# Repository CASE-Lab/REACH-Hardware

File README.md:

# REACH-Hardware
REACH - Rugged Extensible Autonomous Control Hardware

## The REACH Unit
Is a fairly compact linux computer built upon the Nvidia Xavier NX developer kit. The main idea is to make the developer kit rugged and modular/extensible. 

### Fields of Interest
The unit is supposed to be used in the fields of robotics and automation if more robust and/or modular solution is needed. 

Example: A REACH unit is used in a research project with an autonomous jet ski. The rugged enclosure makes it ideal for the harsh environment. Because of it's modularity it also allows for future extensions to meet new needs that can arise. This version of the unit features two camera inputs and telemetry support.

Example: A REACH unit is used for controlling a Husqvarna Research Platform (HRP) (a modified robotic lawn mower for research purposes). It allows for enough computational power to easily run ROS2, while also allowing for a camera and USB devices to be connected in the future. This version of the unit is the standard version with one camera input and GPIO ports.

### Features
* Built upon an Nvidia NX developer kit
* Passively cooled
* Should attain an IP65 rating (untested)
* Allows for use of up to two Raspberry PI cameras over a distance of up to 10m using the HDMI to CSI adapter (adapter found in REACH-Extensions). (Number of supported cameras varies depending on the configuration)
* All standard connectors from the dev kit have been routed to the outside of the enclosure (1x Ethernet port, Wifi, 2-3x USB ports)
* Features up to 4 expansion cards which can add function such as CAN and RS232 support. Each card can be conencted to a standard M12 industrial connector located on the front panel.
* Depending on the configuration the unit features either 2 analogue and 5 digital GPIO pins or telemetry support.

[TOC]

## Getting Started

### Flashing with Nvidia SDK

* Currently requires Ubuntu 18.04 for Nvidia SDK Manager
* Can also be used on newer Ubuntu versions via Docker. [Instructions](https://docs.nvidia.com/sdk-manager/docker-containers/index.html)

### Booting from NVME SSD

* [Jetsonhacks Guide](https://www.jetsonhacks.com/2020/05/29/jetson-xavier-nx-run-from-ssd/)

### Stress testing

* Monitoring using jtop (requires pip for installation)

  ```sh
  # install
  sudo -H pip install -U jetson-stats
  # run
  sudo jtop
  ```

* Stress test GPU (and also CPU indirectly by running multiple instances of glmark2)

  ```sh
  # install
  sudo apt-get install -y glmark2
  # run
  glmark2
  ```

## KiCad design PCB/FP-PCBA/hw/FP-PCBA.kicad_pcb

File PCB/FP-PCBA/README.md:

# FP-PCBA

Front Panel PCB Assembly

* Breaks out USB 3.0 from Jetson development board to front panel
* Holds 4 modular expansion headers

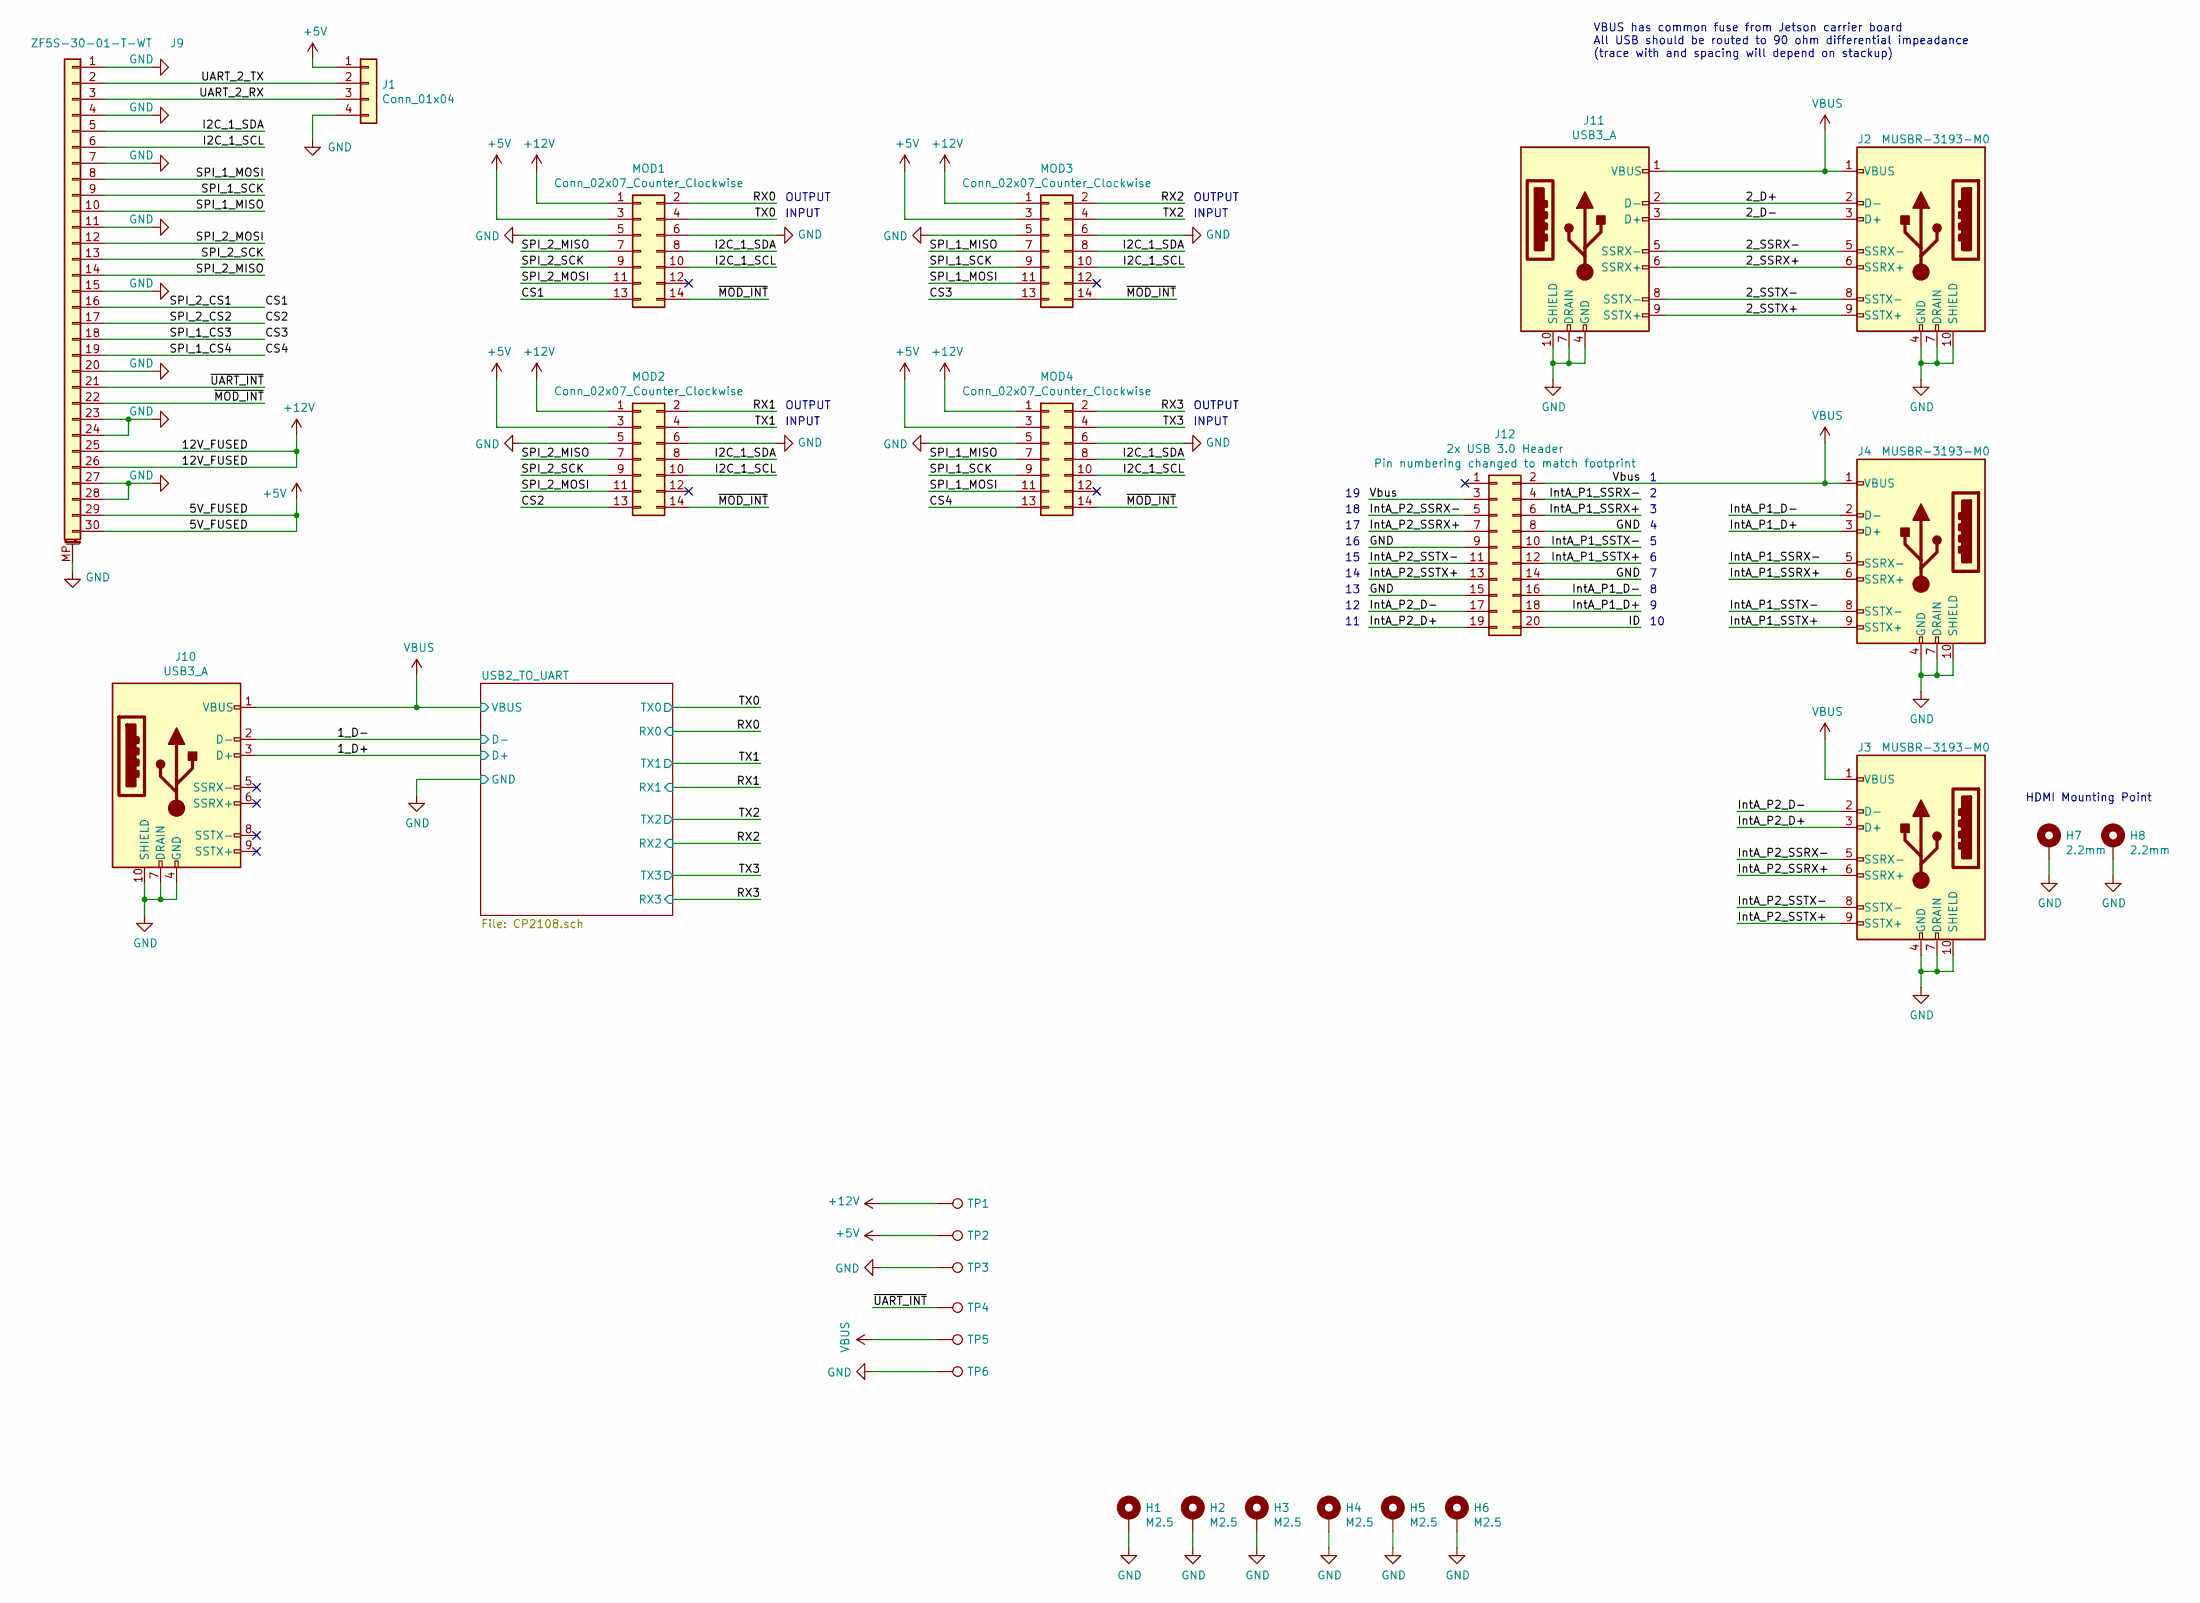
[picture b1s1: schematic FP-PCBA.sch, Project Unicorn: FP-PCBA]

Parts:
H1, H2, H3, H4: M2.5; MountingHole_2.7mm_M2.5_Pad_Via
H5, H6: M2.5; Slotted_2mm_M2.5_Vias
H7, H8: 2.2mm; MountingHole_2.2mm_M2_Pad
J1: Conn_01x04; Molex_Micro_Lock_1x4_Vertical_5055680471; MPN 505568-0471
J2, J3, J4: MUSBR-3193-M0; MUSBR3193M0; MPN MUSBR-3193-M0
J9: ZF5S-30-01-T-WT; ZF5S-30-03-T-WT; MPN ZF5S-30-03-T-WT
J10, J11: USB3_A; USB3_A_Plug_AMPHENOL_GSB316441CEU; MPN GSB316441CEU
J12: 2x USB 3.0 Header; PinHeader_2x10_P2.00mm_Vertical; MPN TW-10-11-T-D-250-080
MOD1, MOD2, MOD3, MOD4: Conn_02x07_Counter_Clockwise; Samtec_HLE-107-02-xxx-DV-BE-A_2x07_P2.54mm_Horizontal; MPN HLE-107-02-F-DV-BE-A-K-TR
TP1, TP2, TP3, TP4, TP5, TP6: TestPoint; TestPoint_THTPad_D1.0mm_Drill0.5mm

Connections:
+5V: J1.1, J9.29, J9.30, MOD1.3, MOD2.3, MOD3.3, MOD4.3, TP2.1
+12V: J9.25, J9.26, MOD1.1, MOD2.1, MOD3.1, MOD4.1, TP1.1
/1_D+: J10.3 (D+); also elsewhere on the board
/1_D-: J10.2 (D-); also elsewhere on the board
/2_D+: J2.2 (D-), J11.2 (D-)
/2_D-: J2.3 (D+), J11.3 (D+)
/2_SSRX+: J2.6 (SSRX+), J11.6 (SSRX+)
/2_SSRX-: J2.5 (SSRX-), J11.5 (SSRX-)
/2_SSTX+: J2.9 (SSTX+), J11.9 (SSTX+)
/2_SSTX-: J2.8 (SSTX-), J11.8 (SSTX-)
/CS1: J9.16, MOD1.13
/CS2: J9.17, MOD2.13
/CS3: J9.18, MOD3.13
/CS4: J9.19, MOD4.13
/I2C_1_SCL: J9.6, MOD1.10, MOD2.10, MOD3.10, MOD4.10
/I2C_1_SDA: J9.5, MOD1.8, MOD2.8, MOD3.8, MOD4.8
/ID: J12.20
/IntA_P1_D+: J4.3 (D+), J12.18
/IntA_P1_D-: J4.2 (D-), J12.16
/IntA_P1_SSRX+: J4.6 (SSRX+), J12.6
/IntA_P1_SSRX-: J4.5 (SSRX-), J12.4
/IntA_P1_SSTX+: J4.9 (SSTX+), J12.12
/IntA_P1_SSTX-: J4.8 (SSTX-), J12.10
/IntA_P2_D+: J3.3 (D+), J12.19
/IntA_P2_D-: J3.2 (D-), J12.17
/IntA_P2_SSRX+: J3.6 (SSRX+), J12.7
/IntA_P2_SSRX-: J3.5 (SSRX-), J12.5
/IntA_P2_SSTX+: J3.9 (SSTX+), J12.13
/IntA_P2_SSTX-: J3.8 (SSTX-), J12.11
/RX0: MOD1.2; also elsewhere on the board
/RX1: MOD2.2; also elsewhere on the board
/RX2: MOD3.2; also elsewhere on the board
/RX3: MOD4.2; also elsewhere on the board
/SPI_1_MISO: J9.10, MOD3.7, MOD4.7
/SPI_1_MOSI: J9.8, MOD3.11, MOD4.11
/SPI_1_SCK: J9.9, MOD3.9, MOD4.9
/SPI_2_MISO: J9.14, MOD1.7, MOD2.7
/SPI_2_MOSI: J9.12, MOD1.11, MOD2.11
/SPI_2_SCK: J9.13, MOD1.9, MOD2.9
/TX0: MOD1.4; also elsewhere on the board
/TX1: MOD2.4; also elsewhere on the board
/TX2: MOD3.4; also elsewhere on the board
/TX3: MOD4.4; also elsewhere on the board
/UART_2_RX: J1.3, J9.3
/UART_2_TX: J1.2, J9.2
/~MOD_INT: J9.22, MOD1.14, MOD2.14, MOD3.14, MOD4.14
/~UART_INT: J9.21, TP4.1
GND: H1.1, H2.1, H3.1, H4.1, H5.1, H6.1, H7.1, H8.1, J1.4, J2.4 (GND), J2.7 (DRAIN), J2.10 (SHIELD), J3.4 (GND), J3.7 (DRAIN), J3.10 (SHIELD), J4.4 (GND), J4.7 (DRAIN), J4.10 (SHIELD), J9.1, J9.4, J9.7, J9.11, J9.15, J9.20, J9.23, J9.24, J9.27, J9.28, J9.MP (MountPin), J10.4 (GND), J10.7 (DRAIN), J10.10 (SHIELD), J11.4 (GND), J11.7 (DRAIN), J11.10 (SHIELD), J12.8, J12.9, J12.14, J12.15, MOD1.5, MOD1.6, MOD2.5, MOD2.6, MOD3.5, MOD3.6, MOD4.5, MOD4.6, TP3.1, TP6.1; also elsewhere on the board
VBUS: J2.1 (VBUS), J3.1 (VBUS), J4.1 (VBUS), J10.1 (VBUS), J11.1 (VBUS), J12.2, J12.3, TP5.1; also elsewhere on the board

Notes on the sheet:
VBUS has common fuse from Jetson carrier board All USB should be routed to 90 ohm differential impeadance (trace with and spacing will depend on stackup)
HDMI Mounting Point
OUTPUT
INPUT

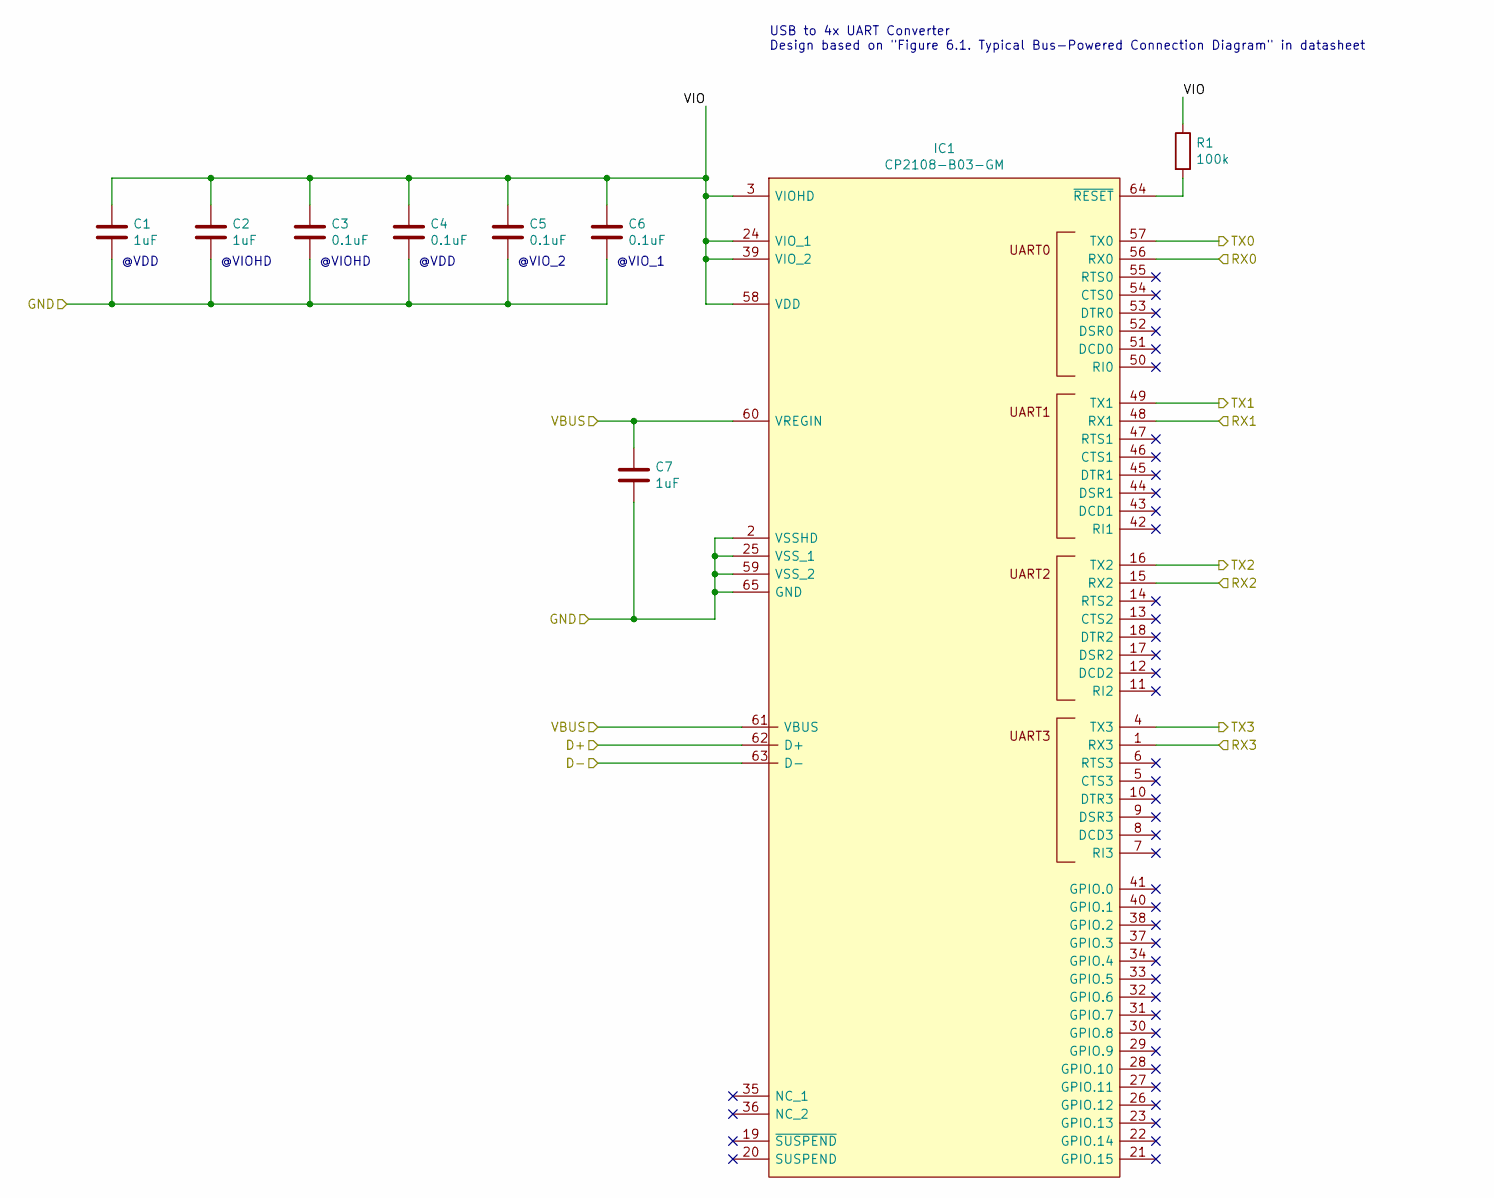
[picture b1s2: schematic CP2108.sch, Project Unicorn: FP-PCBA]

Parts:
C1, C2, C7: 1uF; C_0603_1608Metric; MPN C0603C105K4RAC7411
C3, C4, C5, C6: 0.1uF; C_0603_1608Metric; MPN 06033C104KAT4A
IC1: CP2108-B03-GM; MPN CP2108-B02-GMR
R1: 100k; R_0603_1608Metric

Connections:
/1_D+: IC1.62 (D+); also elsewhere on the board
/1_D-: IC1.63 (D-); also elsewhere on the board
/RX0: IC1.56 (RX0); also elsewhere on the board
/RX1: IC1.48 (RX1); also elsewhere on the board
/RX2: IC1.15 (RX2); also elsewhere on the board
/RX3: IC1.1 (RX3); also elsewhere on the board
/TX0: IC1.57 (TX0); also elsewhere on the board
/TX1: IC1.49 (TX1); also elsewhere on the board
/TX2: IC1.16 (TX2); also elsewhere on the board
/TX3: IC1.4 (TX3); also elsewhere on the board
/USB2_TO_UART/VIO: C1.1, C2.1, C3.1, C4.1, C5.1, C6.1, IC1.3 (VIOHD), IC1.24 (VIO_1), IC1.39 (VIO_2), IC1.58 (VDD), R1.1
GND: C1.2, C2.2, C3.2, C4.2, C5.2, C6.2, C7.2, IC1.2 (VSSHD), IC1.25 (VSS_1), IC1.59 (VSS_2), IC1.65 (GND); also elsewhere on the board
unnamed: IC1.64 (~RESET), R1.2
VBUS: C7.1, IC1.60 (VREGIN), IC1.61 (VBUS); also elsewhere on the board

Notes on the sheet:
@VIO_1
@VIO_2
@VDD
@VIOHD
USB to 4x UART Converter Design based on "Figure 6.1. Typical Bus-Powered Connection Diagram" in datasheet

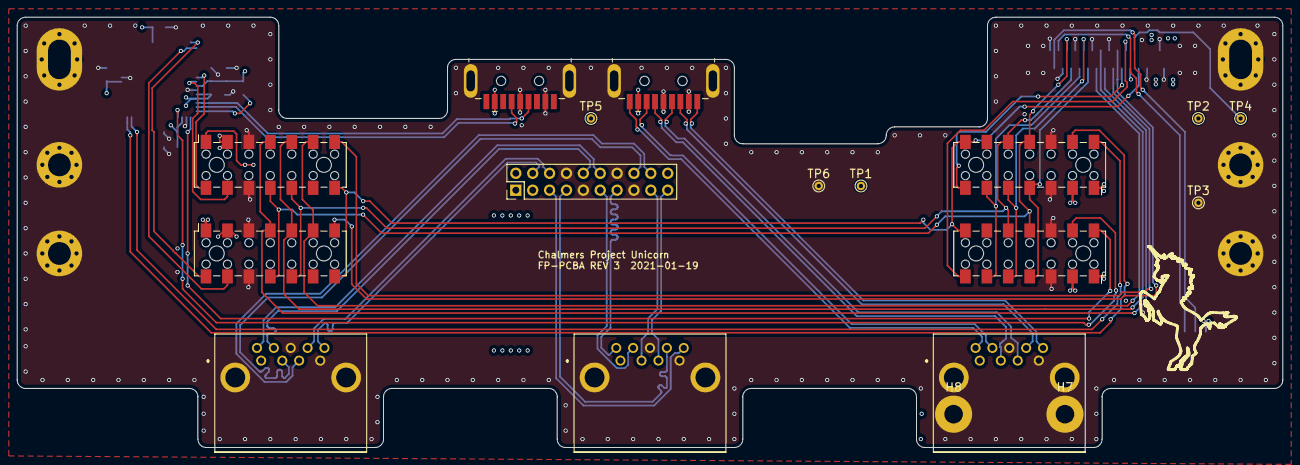
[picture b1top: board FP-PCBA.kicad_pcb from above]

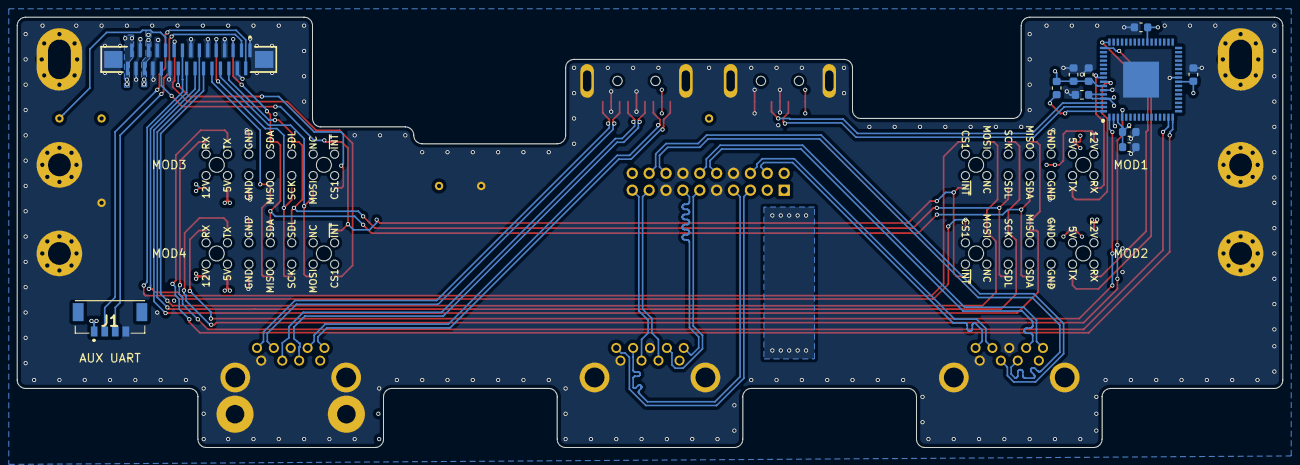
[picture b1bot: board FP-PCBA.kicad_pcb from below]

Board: 4 copper layers, 150.0 x 51.0 mm, 35 parts (11 on the bottom side), 50 nets.

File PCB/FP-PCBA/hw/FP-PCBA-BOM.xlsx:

Project Unicorn: FP-PCBA BOM |  | Chalmers University of Technology
REV: 2 |  | REV Date: 2020-11-12
Reference | Qty | Value | Distributor | Distributor PN | MPN | Manufacturer | DNP | Comments
Non PCB Items
Kicad CSV Imported Items
C4 C5 C6 C3 | 4 | 0.1uF | Mouser | 581-06033C104KAT4A | 06033C104KAT4A | AVX
C7 C2 C1 | 3 | 1uF | Mouser | 80-C0603C105K4RLR | C0603C105K4RAC7411 | KEMET
H1 H2 H3 H4 | 4 | M2.5 |  |  |  |  | DNP
H5 H6 | 2 | M2.5 |  |  |  |  | DNP
H7 H8 | 2 | 2.2mm |  |  |  |  | DNP
IC1 | 1 | CP2108-B03-GM | Mouser | 634-CP2108-B02-GMR | CP2108-B02-GMR | Silicon Labs |  | Change to B03 variant (currently not in stock)
J1 | 1 | Conn_01x04 | Mouser | 538-505568-0471 | 505568-0471 | Molex | DNP | Only populate if used
J10 J11 | 2 | USB3_A | Mouser | 523-GSB316441CEU | GSB316441CEU | Amphenol
J12 | 1 | 2x USB 3.0 Header | Mouser | 200-TW1011TD250080 | TW-10-11-T-D-250-080 | Samtec |  | Pin numbering changed to match footprint
J4 J3 J2 | 3 | MUSBR-3193-M0 | Mouser | 523-MUSBR-3193-M0 | MUSBR-3193-M0 | Amphenol
J9 | 1 | ZF5S-30-01-T-WT | Mouser | 200-ZF5S3003TWTTR | ZF5S-30-03-T-WT | Samtec |  | To FP-PCBA
MOD4 MOD3 MOD2 MOD1 | 4 | Conn_02x07_Counter_Clockwise | Mouser | 200-HLE1072FDVBEAKTR | HLE-107-02-F-DV-BE-A-K-TR | Samtec |  | Check datasheet for compatible variants
R1 | 1 | 100k | CASE
TP3 TP2 TP1 TP5 TP4 TP6 | 6 | TestPoint |  |  |  |  | DNP
0 | 0 | 0 | 0 | 0 | 0 | 0 | 0 | 0
0 | 0 | 0 | 0 | 0 | 0 | 0 | 0 | 0
0 | 0 | 0 | 0 | 0 | 0 | 0 | 0 | 0
0 | 0 | 0 | 0 | 0 | 0 | 0 | 0 | 0
0 | 0 | 0 | 0 | 0 | 0 | 0 | 0 | 0
0 | 0 | 0 | 0 | 0 | 0 | 0 | 0 | 0
0 | 0 | 0 | 0 | 0 | 0 | 0 | 0 | 0
0 | 0 | 0 | 0 | 0 | 0 | 0 | 0 | 0
0 | 0 | 0 | 0 | 0 | 0 | 0 | 0 | 0
0 | 0 | 0 | 0 | 0 | 0 | 0 | 0 | 0
0 | 0 | 0 | 0 | 0 | 0 | 0 | 0 | 0
0 | 0 | 0 | 0 | 0 | 0 | 0 | 0 | 0
0 | 0 | 0 | 0 | 0 | 0 | 0 | 0 | 0
0 | 0 | 0 | 0 | 0 | 0 | 0 | 0 | 0
0 | 0 | 0 | 0 | 0 | 0 | 0 | 0 | 0
0 | 0 | 0 | 0 | 0 | 0 | 0 | 0 | 0
0 | 0 | 0 | 0 | 0 | 0 | 0 | 0 | 0
0 | 0 | 0 | 0 | 0 | 0 | 0 | 0 | 0
0 | 0 | 0 | 0 | 0 | 0 | 0 | 0 | 0
0 | 0 | 0 | 0 | 0 | 0 | 0 | 0 | 0
0 | 0 | 0 | 0 | 0 | 0 | 0 | 0 | 0
0 | 0 | 0 | 0 | 0 | 0 | 0 | 0 | 0
0 | 0 | 0 | 0 | 0 | 0 | 0 | 0 | 0
0 | 0 | 0 | 0 | 0 | 0 | 0 | 0 | 0
0 | 0 | 0 | 0 | 0 | 0 | 0 | 0 | 0
0 | 0 | 0 | 0 | 0 | 0 | 0 | 0 | 0
0 | 0 | 0 | 0 | 0 | 0 | 0 | 0 | 0
0 | 0 | 0 | 0 | 0 | 0 | 0 | 0 | 0
0 | 0 | 0 | 0 | 0 | 0 | 0 | 0 | 0
0 | 0 | 0 | 0 | 0 | 0 | 0 | 0 | 0
0 | 0 | 0 | 0 | 0 | 0 | 0 | 0 | 0
0 | 0 | 0 | 0 | 0 | 0 | 0 | 0 | 0
0 | 0 | 0 | 0 | 0 | 0 | 0 | 0 | 0
0 | 0 | 0 | 0 | 0 | 0 | 0 | 0 | 0
0 | 0 | 0 | 0 | 0 | 0 | 0 | 0 | 0
0 | 0 | 0 | 0 | 0 | 0 | 0 | 0 | 0
0 | 0 | 0 | 0 | 0 | 0 | 0 | 0 | 0
0 | 0 | 0 | 0 | 0 | 0 | 0 | 0 | 0
0 | 0 | 0 | 0 | 0 | 0 | 0 | 0 | 0
0 | 0 | 0 | 0 | 0 | 0 | 0 | 0 | 0
0 | 0 | 0 | 0 | 0 | 0 | 0 | 0 | 0
0 | 0 | 0 | 0 | 0 | 0 | 0 | 0 | 0
0 | 0 | 0 | 0 | 0 | 0 | 0 | 0 | 0
0 | 0 | 0 | 0 | 0 | 0 | 0 | 0 | 0
0 | 0 | 0 | 0 | 0 | 0 | 0 | 0 | 0
0 | 0 | 0 | 0 | 0 | 0 | 0 | 0 | 0
0 | 0 | 0 | 0 | 0 | 0 | 0 | 0 | 0
0 | 0 | 0 | 0 | 0 | 0 | 0 | 0 | 0
0 | 0 | 0 | 0 | 0 | 0 | 0 | 0 | 0
0 | 0 | 0 | 0 | 0 | 0 | 0 | 0 | 0
0 | 0 | 0 | 0 | 0 | 0 | 0 | 0 | 0
0 | 0 | 0 | 0 | 0 | 0 | 0 | 0 | 0
0 | 0 | 0 | 0 | 0 | 0 | 0 | 0 | 0
0 | 0 | 0 | 0 | 0 | 0 | 0 | 0 | 0
0 | 0 | 0 | 0 | 0 | 0 | 0 | 0 | 0
0 | 0 | 0 | 0 | 0 | 0 | 0 | 0 | 0
0 | 0 | 0 | 0 | 0 | 0 | 0 | 0 | 0
0 | 0 | 0 | 0 | 0 | 0 | 0 | 0 | 0
0 | 0 | 0 | 0 | 0 | 0 | 0 | 0 | 0
0 | 0 | 0 | 0 | 0 | 0 | 0 | 0 | 0
0 | 0 | 0 | 0 | 0 | 0 | 0 | 0 | 0
0 | 0 | 0 | 0 | 0 | 0 | 0 | 0 | 0
0 | 0 | 0 | 0 | 0 | 0 | 0 | 0 | 0
0 | 0 | 0 | 0 | 0 | 0 | 0 | 0 | 0
0 | 0 | 0 | 0 | 0 | 0 | 0 | 0 | 0
0 | 0 | 0 | 0 | 0 | 0 | 0 | 0 | 0
0 | 0 | 0 | 0 | 0 | 0 | 0 | 0 | 0
0 | 0 | 0 | 0 | 0 | 0 | 0 | 0 | 0
0 | 0 | 0 | 0 | 0 | 0 | 0 | 0 | 0
0 | 0 | 0 | 0 | 0 | 0 | 0 | 0 | 0
0 | 0 | 0 | 0 | 0 | 0 | 0 | 0 | 0
0 | 0 | 0 | 0 | 0 | 0 | 0 | 0 | 0
0 | 0 | 0 | 0 | 0 | 0 | 0 | 0 | 0
0 | 0 | 0 | 0 | 0 | 0 | 0 | 0 | 0
0 | 0 | 0 | 0 | 0 | 0 | 0 | 0 | 0
0 | 0 | 0 | 0 | 0 | 0 | 0 | 0 | 0
0 | 0 | 0 | 0 | 0 | 0 | 0 | 0 | 0
0 | 0 | 0 | 0 | 0 | 0 | 0 | 0 | 0
0 | 0 | 0 | 0 | 0 | 0 | 0 | 0 | 0
0 | 0 | 0 | 0 | 0 | 0 | 0 | 0 | 0
0 | 0 | 0 | 0 | 0 | 0 | 0 | 0 | 0
0 | 0 | 0 | 0 | 0 | 0 | 0 | 0 | 0
0 | 0 | 0 | 0 | 0 | 0 | 0 | 0 | 0
0 | 0 | 0 | 0 | 0 | 0 | 0 | 0 | 0
0 | 0 | 0 | 0 | 0 | 0 | 0 | 0 | 0
0 | 0 | 0 | 0 | 0 | 0 | 0 | 0 | 0
0 | 0 | 0 | 0 | 0 | 0 | 0 | 0 | 0
0 | 0 | 0 | 0 | 0 | 0 | 0 | 0 | 0
0 | 0 | 0 | 0 | 0 | 0 | 0 | 0 | 0
0 | 0 | 0 | 0 | 0 | 0 | 0 | 0 | 0
0 | 0 | 0 | 0 | 0 | 0 | 0 | 0 | 0
0 | 0 | 0 | 0 | 0 | 0 | 0 | 0 | 0
0 | 0 | 0 | 0 | 0 | 0 | 0 | 0 | 0
0 | 0 | 0 | 0 | 0 | 0 | 0 | 0 | 0
0 | 0 | 0 | 0 | 0 | 0 | 0 | 0 | 0
0 | 0 | 0 | 0 | 0 | 0 | 0 | 0 | 0
0 | 0 | 0 | 0 | 0 | 0 | 0 | 0 | 0
0 | 0 | 0 | 0 | 0 | 0 | 0 | 0 | 0
0 | 0 | 0 | 0 | 0 | 0 | 0 | 0 | 0
0 | 0 | 0 | 0 | 0 | 0 | 0 | 0 | 0
0 | 0 | 0 | 0 | 0 | 0 | 0 | 0 | 0
0 | 0 | 0 | 0 | 0 | 0 | 0 | 0 | 0
0 | 0 | 0 | 0 | 0 | 0 | 0 | 0 | 0
0 | 0 | 0 | 0 | 0 | 0 | 0 | 0 | 0
0 | 0 | 0 | 0 | 0 | 0 | 0 | 0 | 0
0 | 0 | 0 | 0 | 0 | 0 | 0 | 0 | 0
0 | 0 | 0 | 0 | 0 | 0 | 0 | 0 | 0
0 | 0 | 0 | 0 | 0 | 0 | 0 | 0 | 0
0 | 0 | 0 | 0 | 0 | 0 | 0 | 0 | 0
0 | 0 | 0 | 0 | 0 | 0 | 0 | 0 | 0
0 | 0 | 0 | 0 | 0 | 0 | 0 | 0 | 0
0 | 0 | 0 | 0 | 0 | 0 | 0 | 0 | 0
0 | 0 | 0 | 0 | 0 | 0 | 0 | 0 | 0
0 | 0 | 0 | 0 | 0 | 0 | 0 | 0 | 0
0 | 0 | 0 | 0 | 0 | 0 | 0 | 0 | 0
0 | 0 | 0 | 0 | 0 | 0 | 0 | 0 | 0
0 | 0 | 0 | 0 | 0 | 0 | 0 | 0 | 0
0 | 0 | 0 | 0 | 0 | 0 | 0 | 0 | 0
0 | 0 | 0 | 0 | 0 | 0 | 0 | 0 | 0
0 | 0 | 0 | 0 | 0 | 0 | 0 | 0 | 0
0 | 0 | 0 | 0 | 0 | 0 | 0 | 0 | 0
0 | 0 | 0 | 0 | 0 | 0 | 0 | 0 | 0
0 | 0 | 0 | 0 | 0 | 0 | 0 | 0 | 0
0 | 0 | 0 | 0 | 0 | 0 | 0 | 0 | 0
0 | 0 | 0 | 0 | 0 | 0 | 0 | 0 | 0
0 | 0 | 0 | 0 | 0 | 0 | 0 | 0 | 0
0 | 0 | 0 | 0 | 0 | 0 | 0 | 0 | 0
0 | 0 | 0 | 0 | 0 | 0 | 0 | 0 | 0
0 | 0 | 0 | 0 | 0 | 0 | 0 | 0 | 0
0 | 0 | 0 | 0 | 0 | 0 | 0 | 0 | 0
0 | 0 | 0 | 0 | 0 | 0 | 0 | 0 | 0
0 | 0 | 0 | 0 | 0 | 0 | 0 | 0 | 0
0 | 0 | 0 | 0 | 0 | 0 | 0 | 0 | 0
0 | 0 | 0 | 0 | 0 | 0 | 0 | 0 | 0
0 | 0 | 0 | 0 | 0 | 0 | 0 | 0 | 0
0 | 0 | 0 | 0 | 0 | 0 | 0 | 0 | 0
0 | 0 | 0 | 0 | 0 | 0 | 0 | 0 | 0
0 | 0 | 0 | 0 | 0 | 0 | 0 | 0 | 0
0 | 0 | 0 | 0 | 0 | 0 | 0 | 0 | 0
0 | 0 | 0 | 0 | 0 | 0 | 0 | 0 | 0
0 | 0 | 0 | 0 | 0 | 0 | 0 | 0 | 0
0 | 0 | 0 | 0 | 0 | 0 | 0 | 0 | 0
0 | 0 | 0 | 0 | 0 | 0 | 0 | 0 | 0
0 | 0 | 0 | 0 | 0 | 0 | 0 | 0 | 0
0 | 0 | 0 | 0 | 0 | 0 | 0 | 0 | 0
0 | 0 | 0 | 0 | 0 | 0 | 0 | 0 | 0

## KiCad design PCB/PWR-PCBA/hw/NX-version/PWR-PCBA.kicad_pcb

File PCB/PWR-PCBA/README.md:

# PWR-PCBA

Power distribution PCB assembly

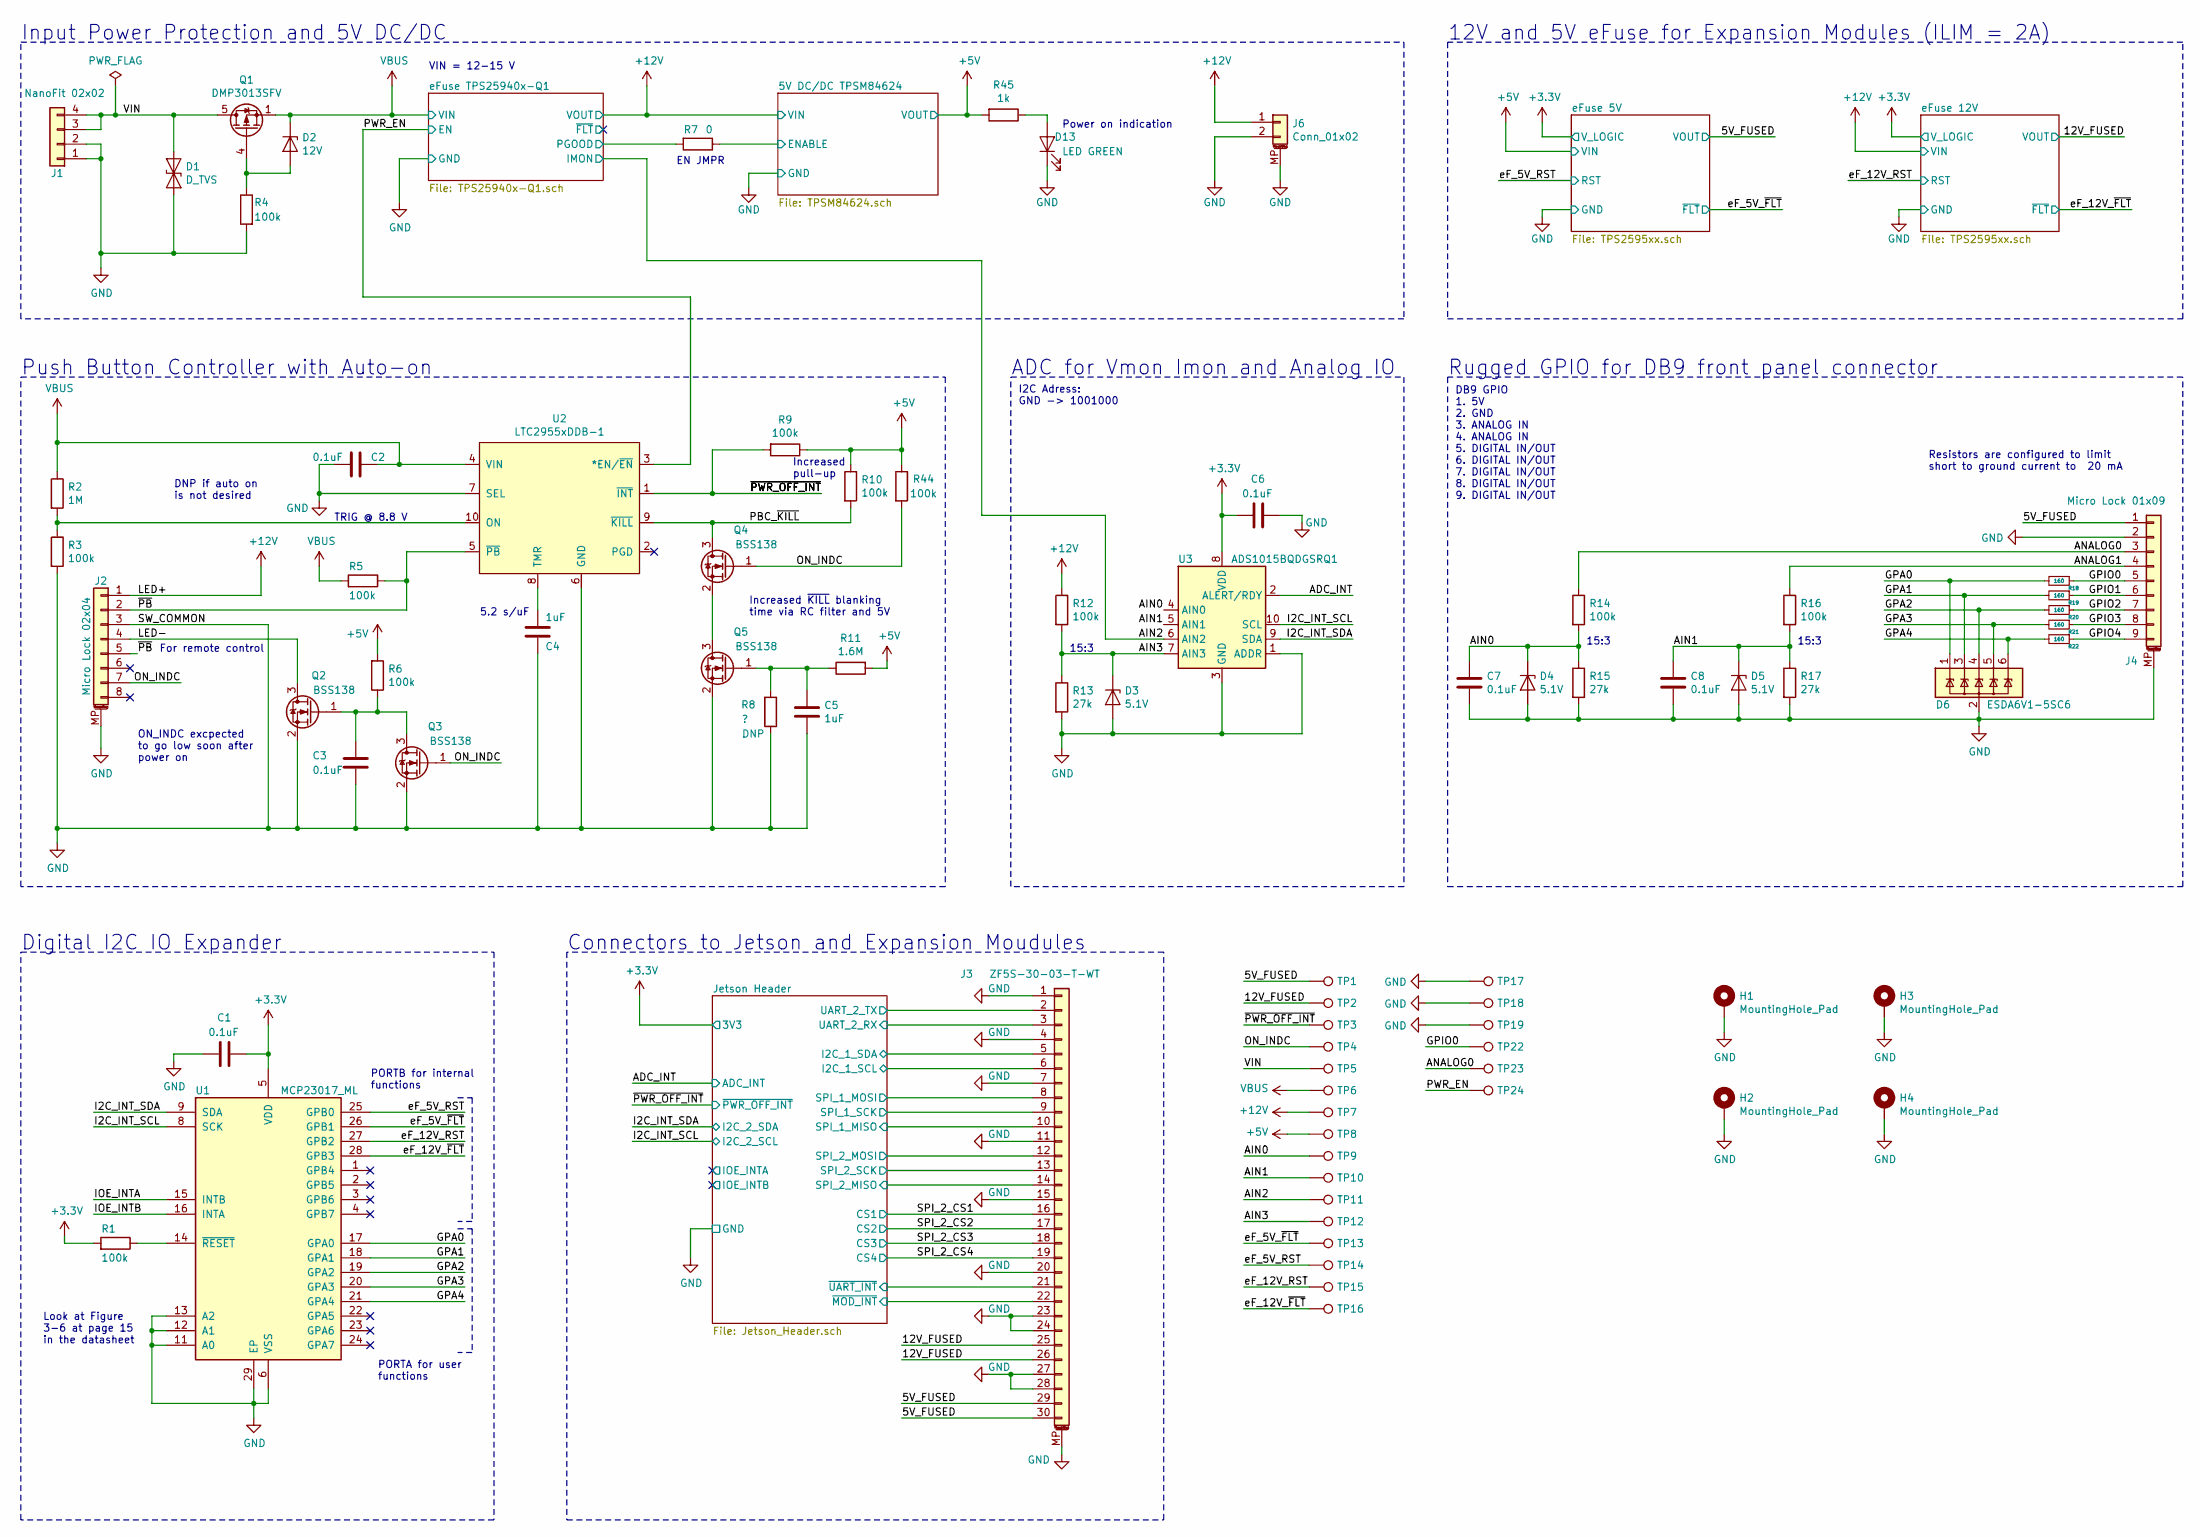
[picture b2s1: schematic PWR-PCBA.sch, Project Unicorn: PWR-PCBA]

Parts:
C1, C2, C3, C6, C7, C8: 0.1uF; C_0603_1608Metric
C4, C5: 1uF; C_0603_1608Metric
D1: D_TVS; D_SMB; MPN TPSMB20CA
D2: 12V; D_SOD-123; MPN MMSZ5242B-G3-08
D3, D4, D5: 5.1V; D_SOD-123; MPN MMSZ5232B-7-F
D6: ESDA6V1-5SC6; SOT-23-6; MPN ESDA6V1-5SC6
D13: LED GREEN; LED_0603_1608Metric
H1, H2, H3, H4: MountingHole_Pad; MountingHole_2.7mm_M2.5_Pad_Via
J1: NanoFit 02x02; 02x02_vertical_105310-1204; MPN 105310-1204
J2: Micro Lock 02x04; Molex_Micro-Lock_5054330871_2x4_P1.25_Vertical; MPN 5054330871
J3: ZF5S-30-03-T-WT; MPN ZF5S-30-03-T-WT-TR
J4: Micro Lock 01x09; 01x09_vertical_2059570971; MPN 205957-0971
J6: Conn_01x02; Molex_Micro-Lock_5055680271_1x02_P1.25_Vertical
Q1: DMP3013SFV; Diodes_PowerDI3333-8; MPN DMP3013SFV-7
Q2, Q3, Q4, Q5: BSS138; SOT-23
R1, R3, R4, R5, R6, R9, R10, R12, R14, R16, R44: 100k; R_0603_1608Metric
R2: 1M; R_0603_1608Metric
R7: 0; R_0603_1608Metric
R8: ?; R_0603_1608Metric
R11: 1.6M; R_0603_1608Metric
R13, R15, R17: 27k; R_0603_1608Metric
R18, R19, R20, R21, R22: 160; R_0603_1608Metric
R45: 1k; R_0603_1608Metric
TP1, TP2, TP3, TP4, TP5, TP6, TP7, TP8, TP9, TP10, TP11, TP12, TP13, TP14, TP15, TP16, TP17, TP18, TP19, TP22, TP23, TP24: TestPoint; TestPoint_THTPad_D1.0mm_Drill0.5mm
U1: MCP23017_ML; QFN-28-1EP_6x6mm_P0.65mm_EP4.25x4.25mm; MPN MCP23017-E/ML
U2: LTC2955xDDB-1; DFN-10-1EP_2x3mm_P0.5mm_EP0.64x2.4mm; MPN LTC2955IDDB-1#TRMPBF
U3: ADS1015BQDGSRQ1; TSSOP-10_3x3mm_P0.5mm; MPN ADS1015BQDGSRQ1

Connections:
+3V3: C1.2, C6.1, R1.2, U1.5 (VDD), U3.8 (VDD); also elsewhere on the board
+5V: R6.2, R9.1, R10.1, R11.2, R44.1, R45.2, TP8.1; also elsewhere on the board
+12V: J2.1, J6.1, R12.1, TP7.1; also elsewhere on the board
/5V DC/DC TPSM84624 /ENABLE: R7.1; also elsewhere on the board
/5V_FUSED: J3.29, J3.30, J4.1, TP1.1; also elsewhere on the board
/12V_FUSED: J3.25, J3.26, TP2.1; also elsewhere on the board
/ADC_INT: U3.2 (ALERT/RDY); also elsewhere on the board
/AIN0: C7.1, D4.1 (K), R14.2, R15.1, TP9.1, U3.4 (AIN0)
/AIN1: C8.1, D5.1 (K), R16.2, R17.1, TP10.1, U3.5 (AIN1)
/AIN2: TP11.1, U3.6 (AIN2); also elsewhere on the board
/AIN3: D3.1 (K), R12.2, R13.1, TP12.1, U3.7 (AIN3)
/ANALOG0: J4.3, R14.1, TP23.1
/ANALOG1: J4.4, R16.1
/GPA0: D6.1 (IO1), R18.2, U1.17 (GPA0)
/GPA1: D6.3 (IO2), R19.2, U1.18 (GPA1)
/GPA2: D6.4 (IO3), R20.2, U1.19 (GPA2)
/GPA3: D6.5 (IO4), R21.2, U1.20 (GPA3)
/GPA4: D6.6 (IO5), R22.2, U1.21 (GPA4)
/GPIO0: J4.5, R18.1, TP22.1
/GPIO1: J4.6, R19.1
/GPIO2: J4.7, R20.1
/GPIO3: J4.8, R21.1
/GPIO4: J4.9, R22.1
/I2C_INT_SCL: U1.8 (SCK), U3.10 (SCL); also elsewhere on the board
/I2C_INT_SDA: U1.9 (SDA), U3.9 (SDA); also elsewhere on the board
/IOE_INTA: U1.15 (INTB)
/IOE_INTB: U1.16 (INTA)
/Jetson Header/I2C_1_SCL: J3.6; also elsewhere on the board
/Jetson Header/I2C_1_SDA: J3.5; also elsewhere on the board
/Jetson Header/SPI_1_MISO: J3.10; also elsewhere on the board
/Jetson Header/SPI_1_MOSI: J3.8; also elsewhere on the board
/Jetson Header/SPI_1_SCK: J3.9; also elsewhere on the board
/Jetson Header/SPI_2_MISO: J3.14; also elsewhere on the board
/Jetson Header/SPI_2_MOSI: J3.12; also elsewhere on the board
/Jetson Header/SPI_2_SCK: J3.13; also elsewhere on the board
/Jetson Header/UART_2_RX: J3.3; also elsewhere on the board
/Jetson Header/UART_2_TX: J3.2; also elsewhere on the board
/Jetson Header/~MOD_INT: J3.22; also elsewhere on the board
/Jetson Header/~UART_INT: J3.21; also elsewhere on the board
/LED-: J2.4, Q2.3 (D)
/ON_INDC: J2.7, Q3.1 (G), Q4.1 (G), R44.2, TP4.1
/PBC_~KILL: Q4.3 (D), R10.2, U2.9 (~KILL)
/PWR_EN: TP24.1, U2.3 (*EN/~EN); also elsewhere on the board
/SPI_2_CS1: J3.16; also elsewhere on the board
/SPI_2_CS2: J3.17; also elsewhere on the board
/SPI_2_CS3: J3.18; also elsewhere on the board
/SPI_2_CS4: J3.19; also elsewhere on the board
/VIN: D1.2 (A2), J1.3, J1.4, Q1.5 (D), TP5.1
/eF_5V_RST: TP14.1, U1.25 (GPB0); also elsewhere on the board
/eF_5V_~FLT: TP13.1, U1.26 (GPB1); also elsewhere on the board
/eF_12V_RST: TP15.1, U1.27 (GPB2); also elsewhere on the board
/eF_12V_~FLT: TP16.1, U1.28 (GPB3); also elsewhere on the board
/eFuse TPS25940x-Q1/PGOOD: R7.2; also elsewhere on the board
/~PB: J2.2, J2.5, R5.1, U2.5 (~PB)
/~PWR_OFF_INT: R9.2, TP3.1, U2.1 (~INT); also elsewhere on the board
GND: C1.1, C2.2, C3.2, C4.2, C5.2, C6.2, C7.2, C8.2, D1.1 (A1), D3.2 (A), D4.2 (A), D5.2 (A), D6.2 (GND), D13.1 (K), H1.1, H2.1, H3.1, H4.1, J1.1, J1.2, J2.3, J2.MP (MountPin), J3.1, J3.4, J3.7, J3.11, J3.15, J3.20, J3.23, J3.24, J3.27, J3.28, J3.MP (MountPin), J4.2, J4.MP (MountPin), J6.2, J6.MP (MountPin), Q2.2 (S), Q3.2 (S), Q5.2 (S), R3.2, R4.2, R8.1, R13.2, R15.2, R17.2, TP17.1, TP18.1, TP19.1, U1.6 (VSS), U1.11 (A0), U1.12 (A1), U1.13 (A2), U1.29 (EP), U2.6 (GND), U2.7 (SEL), U3.1 (ADDR), U3.3 (GND); also elsewhere on the board
unnamed: C3.1, Q2.1 (G), Q3.3 (D), R6.1
unnamed: C4.1, U2.8 (TMR)
unnamed: C5.1, Q5.1 (G), R8.2, R11.1
unnamed: D2.2 (A), Q1.4 (G), R4.1
unnamed: D13.2 (A), R45.1
unnamed: Q4.2 (S), Q5.3 (D)
unnamed: R1.1, U1.14 (~RESET~)
unnamed: R2.2, R3.1, U2.10 (ON)
VBUS: C2.1, D2.1 (K), Q1.1 (S), Q1.2 (S), Q1.3 (S), R2.1, R5.2, TP6.1, U2.4 (VIN); also elsewhere on the board

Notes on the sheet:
VIN = 12-15 V
DNP if auto on is not desired
5.2 s/uF
TRIG @ 8.8 V
I2C Adress: GND -> 1001000
15:3
Push Button Controller with Auto-on
ADC for Vmon Imon and Analog IO
DB9 GPIO 1. 5V 2. GND 3. ANALOG IN 4. ANALOG IN 5. DIGITAL IN/OUT 6. DIGITAL IN/OUT 7. DIGITAL IN/OUT 8. DIGITAL IN/OUT 9. DIGITAL IN/OUT
EN JMPR
Increased ~KILL~ blanking time via RC filter and 5V
Increased pull-up
Rugged GPIO for DB9 front panel connector
Resistors are configured to limit short to ground current to 20 mA
Look at Figure 3-6 at page 15 in the datasheet
PORTA for user functions
PORTB for internal functions
Input Power Protection and 5V DC/DC
12V and 5V eFuse for Expansion Modules (ILIM = 2A)
Digital I2C IO Expander
Connectors to Jetson and Expansion Moudules
For remote control
Power on indication
ON_INDC excpected to go low soon after power on

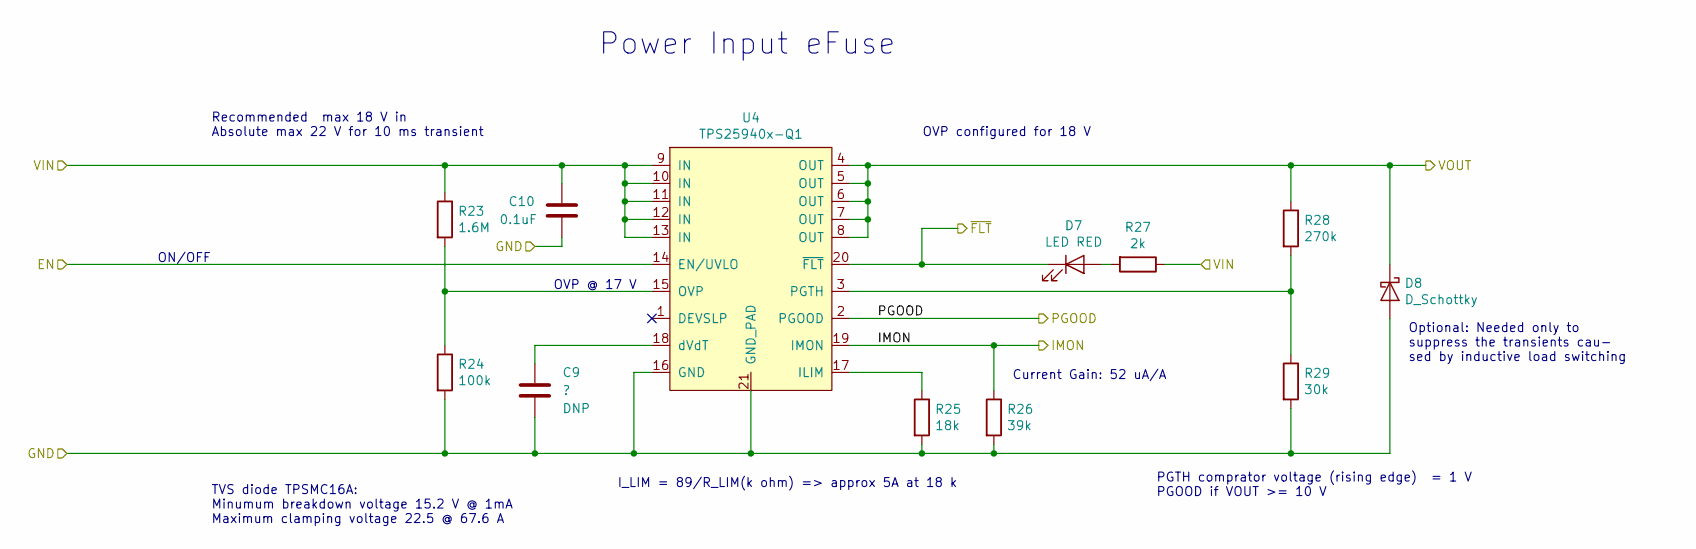
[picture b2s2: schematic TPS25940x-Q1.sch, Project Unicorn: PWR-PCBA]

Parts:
C9: ?; C_0603_1608Metric
C10: 0.1uF; C_0603_1608Metric
D7: LED RED; LED_0603_1608Metric
D8: D_Schottky; D_SOD-123; MPN 1N5819HW
R23: 1.6M; R_0603_1608Metric
R24: 100k; R_0603_1608Metric
R25: 18k; R_0603_1608Metric
R26: 39k; R_0603_1608Metric
R27: 2k; R_0603_1608Metric
R28: 270k; R_0603_1608Metric
R29: 30k; R_0603_1608Metric
U4: TPS25940x-Q1; QFN-20-1EP_3x4mm_P0.5mm_EP1.65x2.65mm_ThermalVias; MPN TPS25940LQRVCRQ1

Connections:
+12V: D8.1 (K), R28.1, U4.4 (OUT), U4.5 (OUT), U4.6 (OUT), U4.7 (OUT), U4.8 (OUT); also elsewhere on the board
/AIN2: R26.1, U4.19 (IMON); also elsewhere on the board
/PWR_EN: U4.14 (EN/UVLO); also elsewhere on the board
/eFuse TPS25940x-Q1/PGOOD: U4.2 (PGOOD); also elsewhere on the board
/eFuse TPS25940x-Q1/~FLT: D7.1 (K), U4.20 (~FLT)
GND: C9.2, C10.2, D8.2 (A), R24.2, R25.2, R26.2, R29.2, U4.16 (GND), U4.21 (GND_PAD); also elsewhere on the board
unnamed: C9.1, U4.18 (dVdT)
unnamed: D7.2 (A), R27.2
unnamed: R23.2, R24.1, U4.15 (OVP)
unnamed: R25.1, U4.17 (ILIM)
unnamed: R28.2, R29.1, U4.3 (PGTH)
VBUS: C10.1, R23.1, R27.1, U4.9 (IN), U4.10 (IN), U4.11 (IN), U4.12 (IN), U4.13 (IN); also elsewhere on the board

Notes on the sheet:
ON/OFF
Power Input eFuse
Recommended max 18 V in Absolute max 22 V for 10 ms transient
I_LIM = 89/R_LIM(k ohm) => approx 5A at 18 k
PGTH comprator voltage (rising edge) = 1 V PGOOD if VOUT >= 10 V
OVP configured for 18 V
Optional: Needed only to suppress the transients cau- sed by inductive load switching
TVS diode TPSMC16A: Minumum breakdown voltage 15.2 V @ 1mA Maximum clamping voltage 22.5 @ 67.6 A
OVP @ 17 V
Current Gain: 52 uA/A

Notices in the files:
parts and their libraries:
Copyright 2016 Accelerated Designs. All rights reserved.
